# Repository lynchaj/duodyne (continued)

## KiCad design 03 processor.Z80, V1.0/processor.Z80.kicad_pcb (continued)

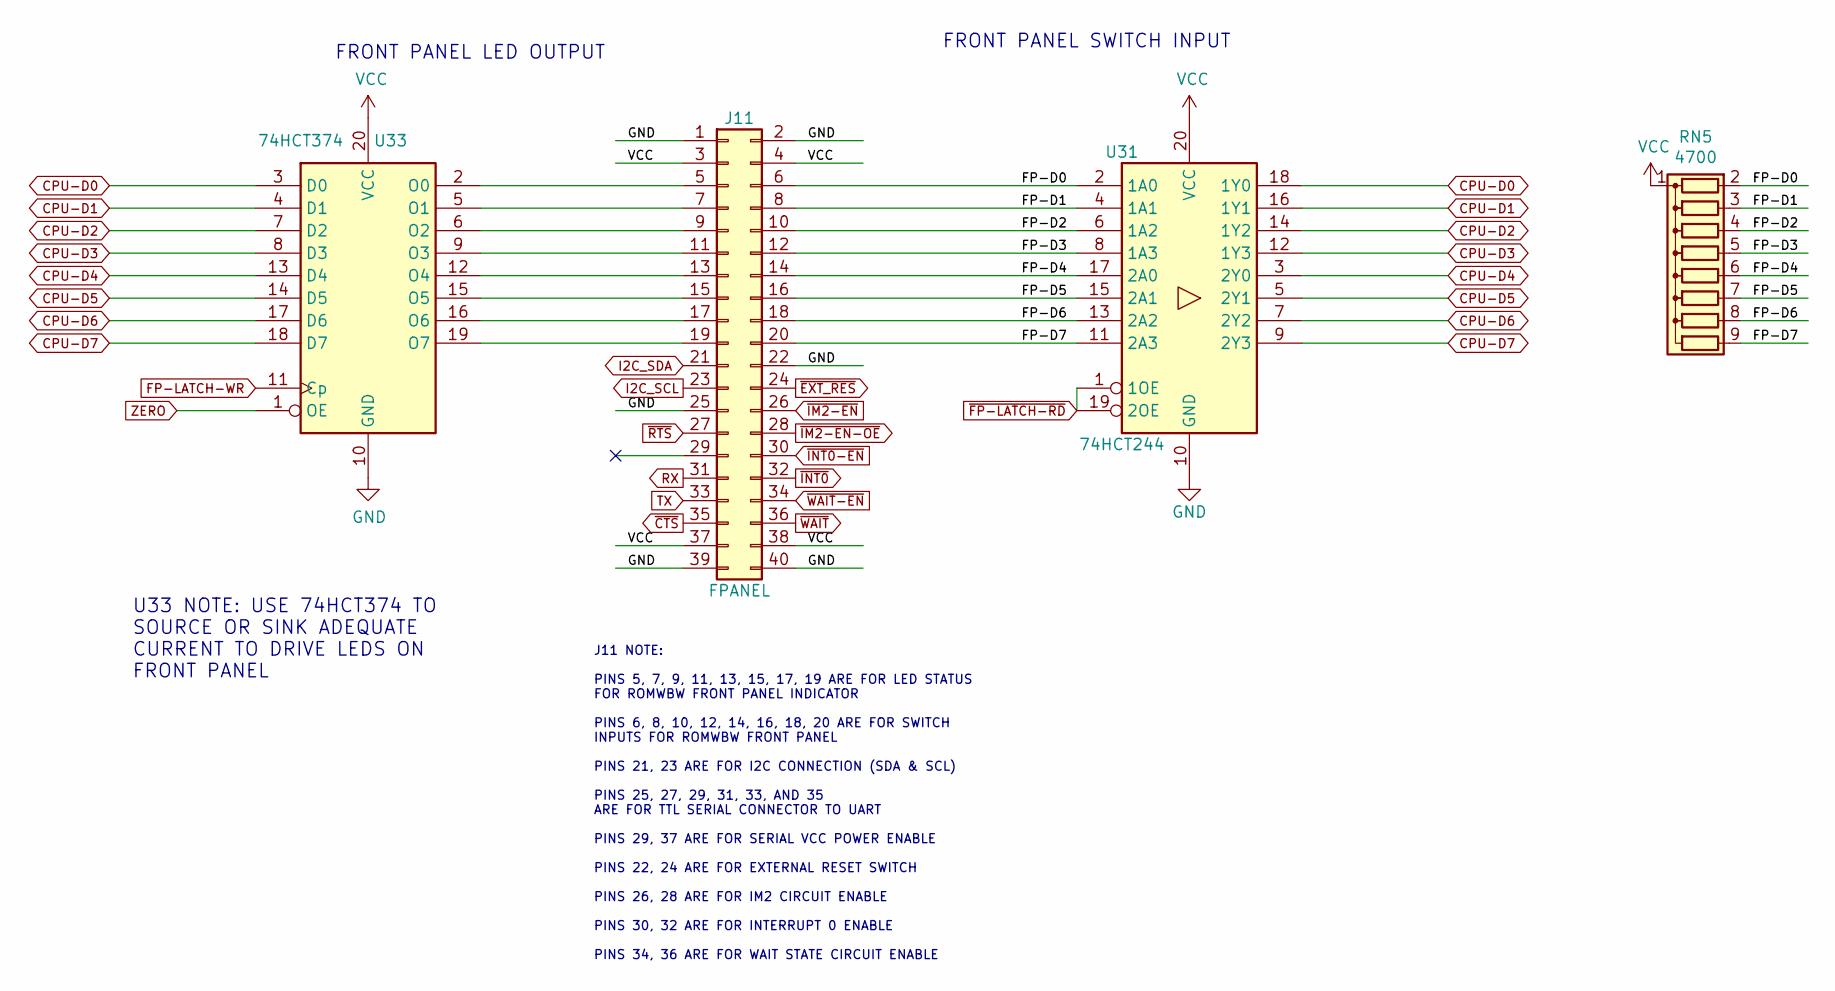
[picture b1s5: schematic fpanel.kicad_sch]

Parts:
J11: FPANEL; IDC-Header_2x20_P2.54mm_Horizontal
RN5: 4700; R_Array_SIP9
U31: 74HCT244; DIP-20_W7.62mm
U33: 74HCT374; DIP-20_W7.62mm

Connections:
/fpanel/FP-D0: J11.6, RN5.2 (R1), U31.2 (1A0)
/fpanel/FP-D1: J11.8, RN5.3 (R2), U31.4 (1A1)
/fpanel/FP-D2: J11.10, RN5.4 (R3), U31.6 (1A2)
/fpanel/FP-D3: J11.12, RN5.5 (R4), U31.8 (1A3)
/fpanel/FP-D4: J11.14, RN5.6 (R5), U31.17 (2A0)
/fpanel/FP-D5: J11.16, RN5.7 (R6), U31.15 (2A1)
/fpanel/FP-D6: J11.18, RN5.8 (R7), U31.13 (2A2)
/fpanel/FP-D7: J11.20, RN5.9 (R8), U31.11 (2A3)
CPU-D0: U31.18 (1Y0), U33.3 (D0); also elsewhere on the board
CPU-D1: U31.16 (1Y1), U33.4 (D1); also elsewhere on the board
CPU-D2: U31.14 (1Y2), U33.7 (D2); also elsewhere on the board
CPU-D3: U31.12 (1Y3), U33.8 (D3); also elsewhere on the board
CPU-D4: U31.3 (2Y0), U33.13 (D4); also elsewhere on the board
CPU-D5: U31.5 (2Y1), U33.14 (D5); also elsewhere on the board
CPU-D6: U31.7 (2Y2), U33.17 (D6); also elsewhere on the board
CPU-D7: U31.9 (2Y3), U33.18 (D7); also elsewhere on the board
FP-LATCH-WR: U33.11 (Cp); also elsewhere on the board
GND: J11.1, J11.2, J11.22, J11.25, J11.39, J11.40, U31.10 (GND), U33.10 (GND); also elsewhere on the board
I2C_SCL: J11.23; also elsewhere on the board
I2C_SDA: J11.21; also elsewhere on the board
unnamed: J11.5, U33.2 (O0)
unnamed: J11.7, U33.5 (O1)
unnamed: J11.9, U33.6 (O2)
unnamed: J11.11, U33.9 (O3)
unnamed: J11.13, U33.12 (O4)
unnamed: J11.15, U33.15 (O5)
unnamed: J11.17, U33.16 (O6)
unnamed: J11.19, U33.19 (O7)
RX: J11.31; also elsewhere on the board
TX: J11.33; also elsewhere on the board
VCC: J11.3, J11.4, J11.37, J11.38, RN5.1 (common), U31.20 (VCC), U33.20 (VCC); also elsewhere on the board
ZERO: U33.1 (OE); also elsewhere on the board
~CTS: J11.35; also elsewhere on the board
~FP-LATCH-RD: U31.1 (1OE), U31.19 (2OE); also elsewhere on the board
~IM2-EN-OE: J11.28; also elsewhere on the board
~IM2-EN: J11.26; also elsewhere on the board
~INT0: J11.32; also elsewhere on the board
~RTS: J11.27; also elsewhere on the board
~WAIT-EN: J11.34; also elsewhere on the board
~WAIT: J11.36; also elsewhere on the board

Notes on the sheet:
J11 NOTE: PINS 5, 7, 9, 11, 13, 15, 17, 19 ARE FOR LED STATUS FOR ROMWBW FRONT PANEL INDICATOR PINS 6, 8, 10, 12, 14, 16, 18, 20 ARE FOR SWITCH INPUTS FOR ROMWBW FRONT PANEL PINS 21, 23 ARE FOR I2C CONNECTION (SDA & SCL) PINS 25, 27, 29, 31, 33, AND 35 ARE FOR TTL SERIAL CONNECTOR TO UART PINS 29, 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
U33 NOTE: USE 74HCT374 TO SOURCE OR SINK ADEQUATE CURRENT TO DRIVE LEDS ON FRONT PANEL
FRONT PANEL SWITCH INPUT
FRONT PANEL LED OUTPUT

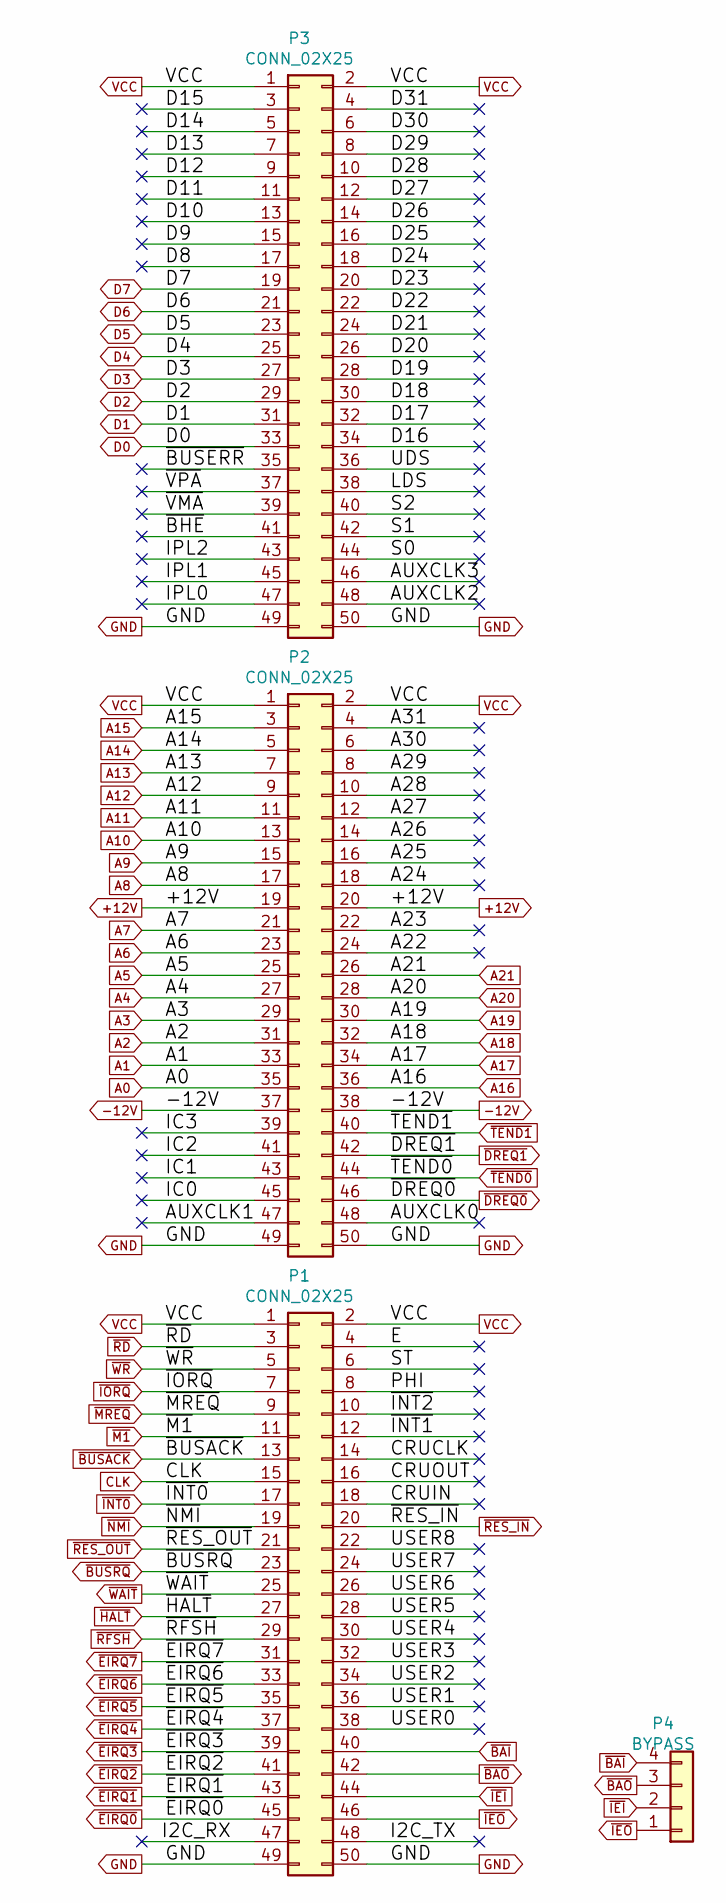
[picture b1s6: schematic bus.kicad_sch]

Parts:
P1, P2, P3: CONN_02X25; IDC-Header_2x25_P2.54mm_Horizontal
P4: BYPASS; PinHeader_1x04_P2.54mm_Vertical

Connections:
+12V: P2.19, P2.20
-12V: P2.37, P2.38
/bus/A22: P2.24
/bus/A23: P2.22
/bus/A24: P2.18
/bus/A25: P2.16
/bus/A26: P2.14
/bus/A27: P2.12
/bus/A28: P2.10
/bus/A29: P2.8
/bus/A30: P2.6
/bus/A31: P2.4
/bus/AUXCLK0: P2.48
/bus/AUXCLK1: P2.47
/bus/AUXCLK2: P3.48
/bus/AUXCLK3: P3.46
/bus/CRUCLK: P1.14
/bus/CRUIN: P1.18
/bus/CRUOUT: P1.16
/bus/D8: P3.17
/bus/D9: P3.15
/bus/D10: P3.13
/bus/D11: P3.11
/bus/D12: P3.9
/bus/D13: P3.7
/bus/D14: P3.5
/bus/D15: P3.3
/bus/D16: P3.34
/bus/D17: P3.32
/bus/D18: P3.30
/bus/D19: P3.28
/bus/D20: P3.26
/bus/D21: P3.24
/bus/D22: P3.22
/bus/D23: P3.20
/bus/D24: P3.18
/bus/D25: P3.16
/bus/D26: P3.14
/bus/D27: P3.12
/bus/D28: P3.10
/bus/D29: P3.8
/bus/D30: P3.6
/bus/D31: P3.4
/bus/E: P1.4
/bus/IC0: P2.45
/bus/IC1: P2.43
/bus/IC2: P2.41
/bus/IC3: P2.39
/bus/IPL0: P3.47
/bus/IPL1: P3.45
/bus/IPL2: P3.43
/bus/LDS: P3.38
/bus/PHI: P1.8
/bus/S0: P3.44
/bus/S1: P3.42
/bus/S2: P3.40
/bus/ST: P1.6
/bus/UDS: P3.36
/bus/USER0: P1.38
/bus/USER1: P1.36
/bus/USER2: P1.34
/bus/USER3: P1.32
/bus/USER4: P1.30
/bus/USER5: P1.28
/bus/USER6: P1.26
/bus/USER7: P1.24
/bus/USER8: P1.22
/bus/~BHE: P3.41
/bus/~BUSERR: P3.35
/bus/~INT1: P1.12
/bus/~INT2: P1.10
/bus/~VMA: P3.39
/bus/~VPA: P3.37
A0: P2.35; also elsewhere on the board
A1: P2.33; also elsewhere on the board
A2: P2.31; also elsewhere on the board
A3: P2.29; also elsewhere on the board
A4: P2.27; also elsewhere on the board
A5: P2.25; also elsewhere on the board
A6: P2.23; also elsewhere on the board
A7: P2.21; also elsewhere on the board
A8: P2.17; also elsewhere on the board
A9: P2.15; also elsewhere on the board
A10: P2.13; also elsewhere on the board
A11: P2.11; also elsewhere on the board
A12: P2.9; also elsewhere on the board
A13: P2.7; also elsewhere on the board
A14: P2.5; also elsewhere on the board
A15: P2.3; also elsewhere on the board
A16: P2.36; also elsewhere on the board
A17: P2.34; also elsewhere on the board
A18: P2.32; also elsewhere on the board
A19: P2.30; also elsewhere on the board
A20: P2.28; also elsewhere on the board
A21: P2.26; also elsewhere on the board
CLK: P1.15; also elsewhere on the board
D0: P3.33; also elsewhere on the board
D1: P3.31; also elsewhere on the board
D2: P3.29; also elsewhere on the board
D3: P3.27; also elsewhere on the board
D4: P3.25; also elsewhere on the board
D5: P3.23; also elsewhere on the board
D6: P3.21; also elsewhere on the board
D7: P3.19; also elsewhere on the board
GND: P1.49, P1.50, P2.49, P2.50, P3.49, P3.50; also elsewhere on the board
I2C_SCL: P1.47; also elsewhere on the board
I2C_SDA: P1.48; also elsewhere on the board
VCC: P1.1, P1.2, P2.1, P2.2, P3.1, P3.2; also elsewhere on the board
~BAI: P1.40, P4.4
~BAO: P1.42, P4.3; also elsewhere on the board
~BUSACK: P1.13; also elsewhere on the board
~BUSRQ: P1.23; also elsewhere on the board
~DREQ0: P2.46; also elsewhere on the board
~DREQ1: P2.42; also elsewhere on the board
~EIRQ0: P1.45; also elsewhere on the board
~EIRQ1: P1.43; also elsewhere on the board
~EIRQ2: P1.41; also elsewhere on the board
~EIRQ3: P1.39; also elsewhere on the board
~EIRQ4: P1.37; also elsewhere on the board
~EIRQ5: P1.35; also elsewhere on the board
~EIRQ6: P1.33; also elsewhere on the board
~EIRQ7: P1.31; also elsewhere on the board
~HALT: P1.27; also elsewhere on the board
~IEI: P1.44, P4.2; also elsewhere on the board
~IEO: P1.46, P4.1; also elsewhere on the board
~INT0: P1.17; also elsewhere on the board
~IORQ: P1.7; also elsewhere on the board
~M1: P1.11; also elsewhere on the board
~MREQ: P1.9; also elsewhere on the board
~NMI: P1.19; also elsewhere on the board
~RD: P1.3; also elsewhere on the board
~RES_IN: P1.20; also elsewhere on the board
~RES_OUT: P1.21; also elsewhere on the board
~RFSH: P1.29; also elsewhere on the board
~TEND0: P2.44; also elsewhere on the board
~TEND1: P2.40; also elsewhere on the board
~WAIT: P1.25; also elsewhere on the board
~WR: P1.5; also elsewhere on the board

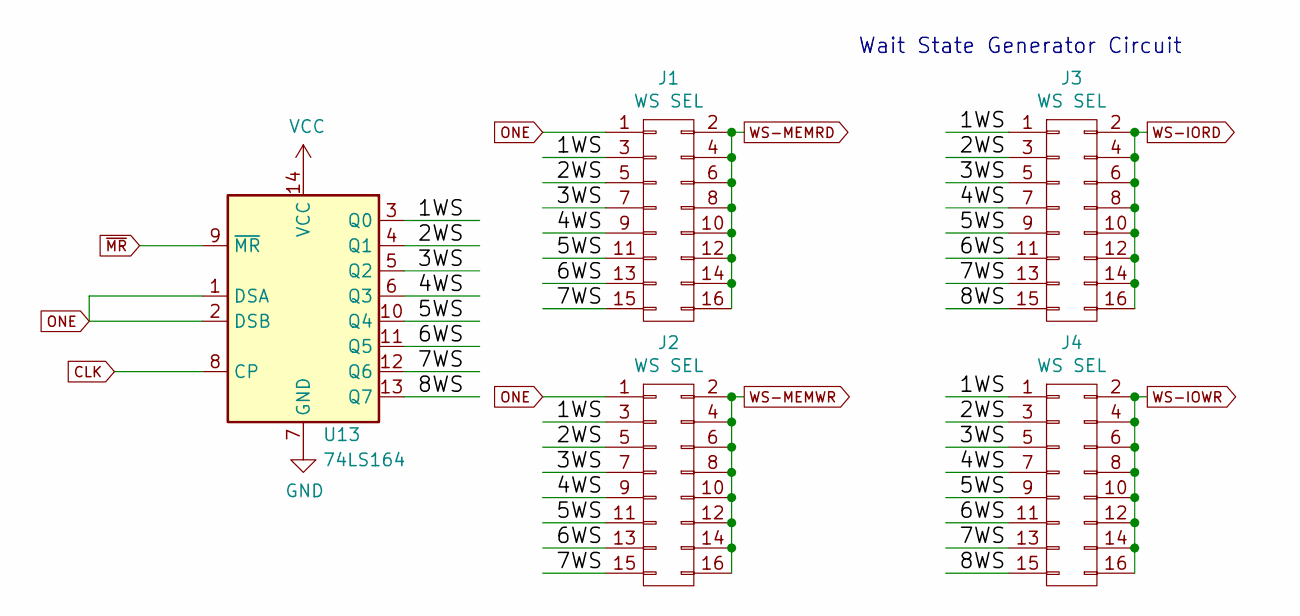
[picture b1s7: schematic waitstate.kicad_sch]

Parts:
J1, J2, J3, J4: WS SEL; PinHeader_2x08_P2.54mm_Vertical
U13: 74LS164; DIP-14_W7.62mm

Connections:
/waitstate/1WS: J1.3, J2.3, J3.1, J4.1, U13.3 (Q0)
/waitstate/2WS: J1.5, J2.5, J3.3, J4.3, U13.4 (Q1)
/waitstate/3WS: J1.7, J2.7, J3.5, J4.5, U13.5 (Q2)
/waitstate/4WS: J1.9, J2.9, J3.7, J4.7, U13.6 (Q3)
/waitstate/5WS: J1.11, J2.11, J3.9, J4.9, U13.10 (Q4)
/waitstate/6WS: J1.13, J2.13, J3.11, J4.11, U13.11 (Q5)
/waitstate/7WS: J1.15, J2.15, J3.13, J4.13, U13.12 (Q6)
/waitstate/8WS: J3.15, J4.15, U13.13 (Q7)
CLK: U13.8 (CP); also elsewhere on the board
GND: U13.7 (GND); also elsewhere on the board
ONE: J1.1, J2.1, U13.1 (DSA), U13.2 (DSB); also elsewhere on the board
VCC: U13.14 (VCC); also elsewhere on the board
WS-IORD: J3.2, J3.4, J3.6, J3.8, J3.10, J3.12, J3.14, J3.16; also elsewhere on the board
WS-IOWR: J4.2, J4.4, J4.6, J4.8, J4.10, J4.12, J4.14, J4.16; also elsewhere on the board
WS-MEMRD: J1.2, J1.4, J1.6, J1.8, J1.10, J1.12, J1.14, J1.16; also elsewhere on the board
WS-MEMWR: J2.2, J2.4, J2.6, J2.8, J2.10, J2.12, J2.14, J2.16; also elsewhere on the board
~MR: U13.9 (~MR); also elsewhere on the board

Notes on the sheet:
Wait State Generator Circuit

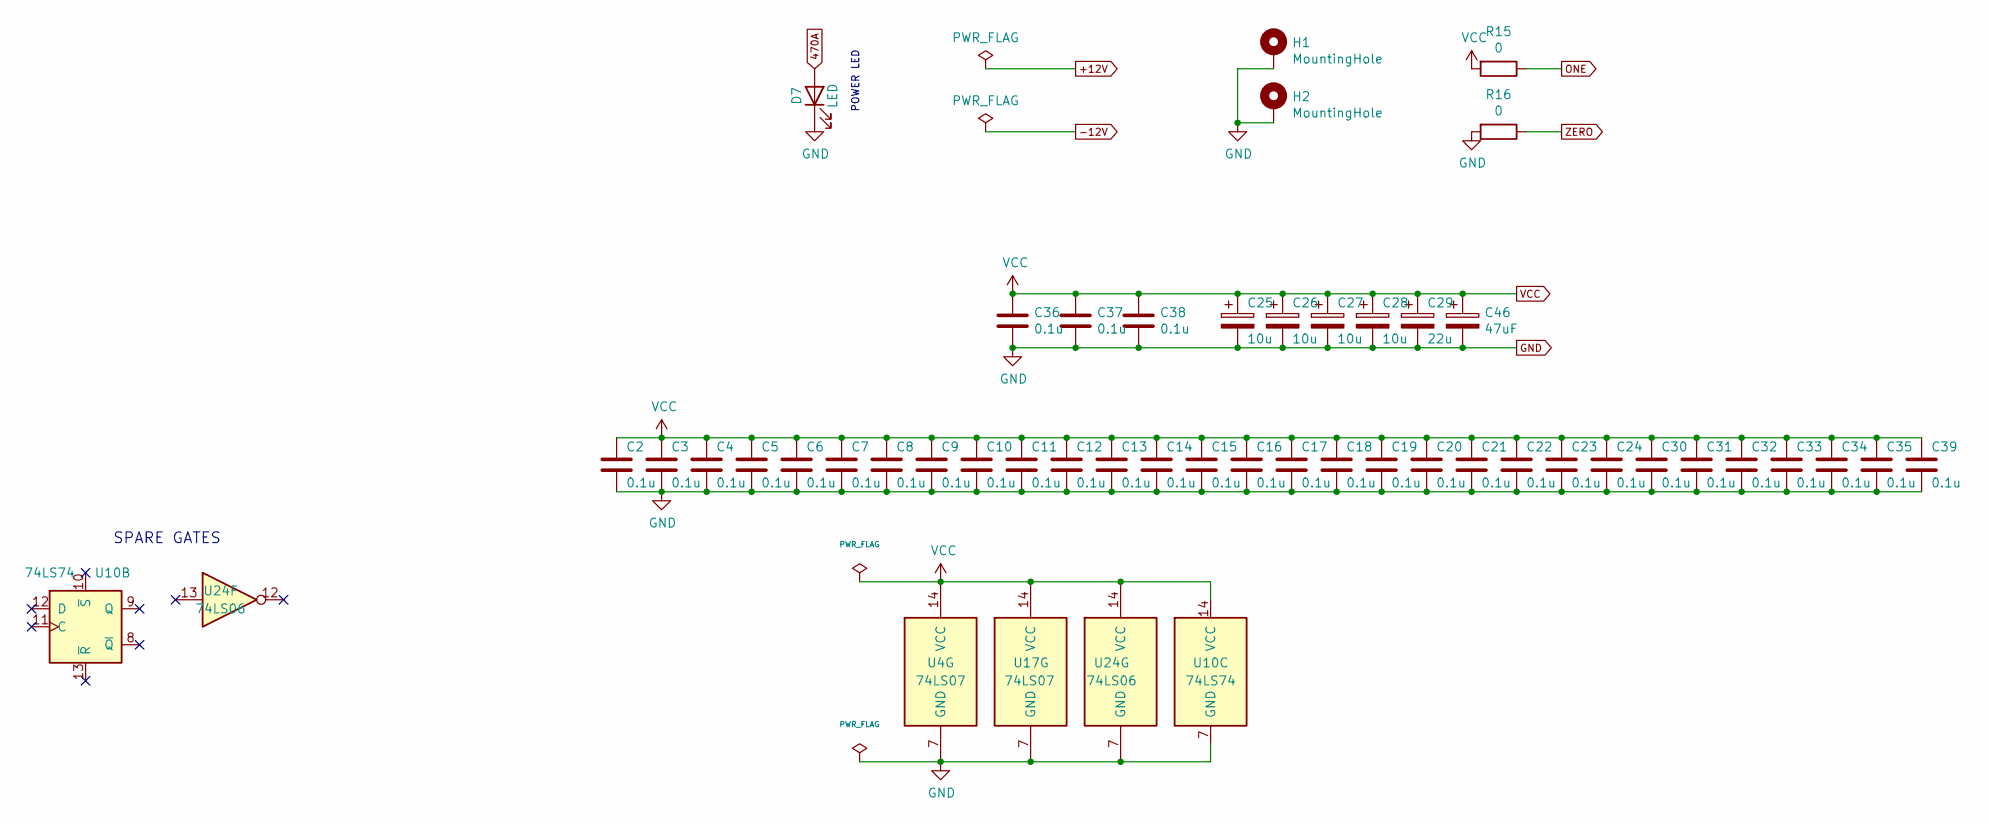
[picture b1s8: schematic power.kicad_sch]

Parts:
C2, C3, C4, C5, C6, C7, C8, C9, C10, C11, C12, C13, C14, C15, C16, C17, C18, C19, C20, C21, C22, C23, C24, C30, C31, C32, C33, C34, C35, C36, C37, C38, C39: 0.1u; C_Disc_D5.0mm_W2.5mm_P5.00mm
C25, C26, C27, C28: 10u; CP_Radial_D5.0mm_P2.50mm
C29: 22u; CP_Radial_D6.3mm_P2.50mm
C46: 47uF; CP_Radial_D5.0mm_P2.50mm
D7: LED; LED_D3.0mm_Horizontal_O3.81mm_Z2.0mm
H1, H2: MountingHole; MountingHole_3.2mm_M3_Pad
R15, R16: 0; R_Axial_DIN0207_L6.3mm_D2.5mm_P7.62mm_Horizontal
U4, U17: 74LS07; DIP-14_W7.62mm
U10: 74LS74; DIP-14_W7.62mm
U24: 74LS06; DIP-14_W7.62mm

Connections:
470A: D7.2 (A); also elsewhere on the board
GND: C2.2, C3.2, C4.2, C5.2, C6.2, C7.2, C8.2, C9.2, C10.2, C11.2, C12.2, C13.2, C14.2, C15.2, C16.2, C17.2, C18.2, C19.2, C20.2, C21.2, C22.2, C23.2, C24.2, C25.2, C26.2, C27.2, C28.2, C29.2, C30.2, C31.2, C32.2, C33.2, C34.2, C35.2, C36.2, C37.2, C38.2, C39.2, C46.2, D7.1 (K), H1.1, H2.1, R16.2, U4.7 (GND), U10.7 (GND), U17.7 (GND), U24.7 (GND); also elsewhere on the board
INT-I2C: U24.13; also elsewhere on the board
unnamed 185: U24.12; also elsewhere on the board
VCC: C2.1, C3.1, C4.1, C5.1, C6.1, C7.1, C8.1, C9.1, C10.1, C11.1, C12.1, C13.1, C14.1, C15.1, C16.1, C17.1, C18.1, C19.1, C20.1, C21.1, C22.1, C23.1, C24.1, C25.1, C26.1, C27.1, C28.1, C29.1, C30.1, C31.1, C32.1, C33.1, C34.1, C35.1, C36.1, C37.1, C38.1, C39.1, C46.1, R15.2, U4.14 (VCC), U10.14 (VCC), U17.14 (VCC), U24.14 (VCC); also elsewhere on the board

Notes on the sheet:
POWER LED
SPARE GATES

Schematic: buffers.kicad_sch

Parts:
JP7: BUS CPU; PinHeader_2x04_P2.54mm_Vertical
R8, R9: 4700; R_Axial_DIN0207_L6.3mm_D2.5mm_P7.62mm_Horizontal
R10: 1800; R_Axial_DIN0207_L6.3mm_D2.5mm_P7.62mm_Horizontal
RN1, RN4: 4700; R_Array_SIP9
U1, U5, U6, U11, U23: 74LS244; DIP-20_W7.62mm
U8: 74LS245; DIP-20_W7.62mm

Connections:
A0: U1.18 (1Y0); also elsewhere on the board
A1: U1.16 (1Y1); also elsewhere on the board
A2: U1.14 (1Y2); also elsewhere on the board
A3: U1.12 (1Y3); also elsewhere on the board
A4: U1.3 (2Y0); also elsewhere on the board
A5: U1.5 (2Y1); also elsewhere on the board
A6: U1.7 (2Y2); also elsewhere on the board
A7: U1.9 (2Y3); also elsewhere on the board
A8: U5.18 (1Y0); also elsewhere on the board
A9: U5.16 (1Y1); also elsewhere on the board
A10: U5.14 (1Y2); also elsewhere on the board
A11: U5.12 (1Y3); also elsewhere on the board
A12: U5.3 (2Y0); also elsewhere on the board
A13: U5.5 (2Y1); also elsewhere on the board
A14: U5.7 (2Y2); also elsewhere on the board
A15: U5.9 (2Y3); also elsewhere on the board
A16: U23.18 (1Y0); also elsewhere on the board
A17: U23.16 (1Y1); also elsewhere on the board
A18: U23.14 (1Y2); also elsewhere on the board
A19: U23.12 (1Y3); also elsewhere on the board
A20: U23.3 (2Y0); also elsewhere on the board
A21: U23.5 (2Y1); also elsewhere on the board
BUSACK: U1.1 (1OE), U1.19 (2OE), U5.1 (1OE), U5.19 (2OE), U11.19 (2OE), U23.1 (1OE), U23.19 (2OE); also elsewhere on the board
CLK: U6.16 (1Y1); also elsewhere on the board
CPU-A0: U1.2 (1A0); also elsewhere on the board
CPU-A1: U1.4 (1A1); also elsewhere on the board
CPU-A2: U1.6 (1A2); also elsewhere on the board
CPU-A3: U1.8 (1A3); also elsewhere on the board
CPU-A4: U1.17 (2A0); also elsewhere on the board
CPU-A5: U1.15 (2A1); also elsewhere on the board
CPU-A6: U1.13 (2A2); also elsewhere on the board
CPU-A7: U1.11 (2A3); also elsewhere on the board
CPU-A8: U5.2 (1A0); also elsewhere on the board
CPU-A9: U5.4 (1A1); also elsewhere on the board
CPU-A10: U5.6 (1A2); also elsewhere on the board
CPU-A11: U5.8 (1A3); also elsewhere on the board
CPU-A12: U5.17 (2A0); also elsewhere on the board
CPU-A13: U5.15 (2A1); also elsewhere on the board
CPU-D0: U8.2 (A0); also elsewhere on the board
CPU-D1: U8.3 (A1); also elsewhere on the board
CPU-D2: U8.4 (A2); also elsewhere on the board
CPU-D3: U8.5 (A3); also elsewhere on the board
CPU-D4: U8.6 (A4); also elsewhere on the board
CPU-D5: U8.7 (A5); also elsewhere on the board
CPU-D6: U8.8 (A6); also elsewhere on the board
CPU-D7: U8.9 (A7); also elsewhere on the board
D0: U8.18 (B0); also elsewhere on the board
D1: U8.17 (B1); also elsewhere on the board
D2: U8.16 (B2); also elsewhere on the board
D3: U8.15 (B3); also elsewhere on the board
D4: U8.14 (B4); also elsewhere on the board
D5: U8.13 (B5); also elsewhere on the board
D6: U8.12 (B6); also elsewhere on the board
D7: U8.11 (B7); also elsewhere on the board
DATA-DIR: U8.1 (A->B); also elsewhere on the board
GND: U1.10 (GND), U5.10 (GND), U6.10 (GND), U8.10 (GND), U11.10 (GND), U23.10 (GND); also elsewhere on the board
unnamed: JP7.1, RN4.6 (R5)
unnamed: JP7.3, RN4.7 (R6)
unnamed: JP7.5, RN4.8 (R7)
unnamed: JP7.7, RN4.9 (R8)
RAW-CLK: U6.4 (1A1); also elsewhere on the board
SEL-A14: U5.13 (2A2); also elsewhere on the board
SEL-A15: U5.11 (2A3); also elsewhere on the board
VCC: R8.1, R9.1, R10.1, RN1.1 (common), RN4.1 (common), U1.20 (VCC), U5.20 (VCC), U6.20 (VCC), U8.20 (VCC), U11.20 (VCC), U23.20 (VCC); also elsewhere on the board
ZERO: U6.1 (1OE), U6.19 (2OE), U11.1 (1OE); also elsewhere on the board
mA16: U23.2 (1A0); also elsewhere on the board
mA17: U23.4 (1A1); also elsewhere on the board
mA18: U23.6 (1A2); also elsewhere on the board
mA19: U23.8 (1A3); also elsewhere on the board
mA20: U23.17 (2A0); also elsewhere on the board
mA21: U23.15 (2A1); also elsewhere on the board
~BAO: RN1.9 (R8), RN4.2 (R1); also elsewhere on the board
~BUS-EN: U8.19 (CE); also elsewhere on the board
~BUSACK: U11.18 (1Y0); also elsewhere on the board
~BUSRQ: R10.2, U6.15 (2A1); also elsewhere on the board
~CPU-BUSRQ: U6.5 (2Y1); also elsewhere on the board
~CPU-HALT: U11.4 (1A1); also elsewhere on the board
~CPU-INT: U6.12 (1Y3); also elsewhere on the board
~CPU-IORQ: RN1.8 (R7), U11.17 (2A0); also elsewhere on the board
~CPU-M1: U11.8 (1A3); also elsewhere on the board
~CPU-MREQ: U11.15 (2A1); also elsewhere on the board
~CPU-NMI: U6.14 (1Y2); also elsewhere on the board
~CPU-RD: U11.11 (2A3); also elsewhere on the board
~CPU-RESET: RN4.5 (R4), U6.18 (1Y0); also elsewhere on the board
~CPU-RFSH: U11.6 (1A2); also elsewhere on the board
~CPU-WAIT: U6.3 (2Y0); also elsewhere on the board
~CPU-WR: U11.13 (2A2); also elsewhere on the board
~DMA-ADDR: RN1.7 (R6); also elsewhere on the board
~DMA-BAO2: U11.2 (1A0); also elsewhere on the board
~DMA-IEI1: U6.9 (2Y3); also elsewhere on the board
~DREQ0: R8.2; also elsewhere on the board
~DREQ1: R9.2; also elsewhere on the board
~HALT: U11.16 (1Y1); also elsewhere on the board
~IEI: RN1.3 (R2), U6.11 (2A3); also elsewhere on the board
~INT0: RN1.5 (R4), U6.8 (1A3); also elsewhere on the board
~IORQ: JP7.2, U11.3 (2Y0); also elsewhere on the board
~M1: U11.12 (1Y3); also elsewhere on the board
~MREQ: JP7.4, U11.5 (2Y1); also elsewhere on the board
~NMI: RN1.4 (R3), U6.6 (1A2); also elsewhere on the board
~RD: JP7.8, U11.9 (2Y3); also elsewhere on the board
~RES_OUT: RN1.2 (R1), U6.2 (1A0); also elsewhere on the board
~RFSH: U11.14 (1Y2); also elsewhere on the board
~TEND0: RN4.3 (R2); also elsewhere on the board
~TEND1: RN4.4 (R3); also elsewhere on the board
~WAIT: RN1.6 (R5), U6.17 (2A0); also elsewhere on the board
~WR: JP7.6, U11.7 (2Y2); also elsewhere on the board

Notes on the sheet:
Z80 BUS INTERFACE

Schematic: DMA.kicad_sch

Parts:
D6, D8, D9, D10, D11, D12: LED; LED_D3.0mm_Horizontal_O3.81mm_Z2.0mm
JP4: IO PORT ADDR; PinHeader_2x06_P2.54mm_Vertical
JP5: INT EN; PinHeader_1x02_P2.54mm_Horizontal
JP6: DMA2 BYPASS; PinHeader_1x04_P2.54mm_Vertical
JP8: DMA1 BYPASS; PinHeader_1x04_P2.54mm_Vertical
JP9: BAO SEL; PinHeader_1x03_P2.54mm_Vertical
NT1, NT2: NetTie_2; NetTie-2_THT_Pad0.3mm
R21: 470; R_Axial_DIN0207_L6.3mm_D2.5mm_P7.62mm_Horizontal
RN3: 10K; R_Array_SIP9
RN6: 4700; R_Array_SIP9
RN9: 470; R_Array_SIP9
U4, U17: 74LS07; DIP-14_W7.62mm
U18, U19: DMA-PLCC-44-CMOS; PLCC-44_THT-Socket; Manufacturer_Part_Number Z84C4206PEG; Mouser Part Number 692-Z84C4206PEG
U20: 74LS175; DIP-16_W7.62mm
U21: 74LS688; DIP-20_W7.62mm
U24: 74LS06
U32: ATtiny13-20PU; DIP-8_W7.62mm

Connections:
10KA: RN3.9 (R8); also elsewhere on the board
470A: RN9.2 (R1); also elsewhere on the board
470B: D6.2 (A), RN9.3 (R2)
470C: RN9.4 (R3); also elsewhere on the board
470D: RN9.5 (R4); also elsewhere on the board
470E: D11.2 (A), RN9.6 (R5)
470F: D8.2 (A), RN9.7 (R6)
470G: D9.2 (A), RN9.8 (R7)
470H: D12.2 (A), RN9.9 (R8)
/DMA/GND-DMA1: NT1.2, U19.34 (GND)
/DMA/GND-DMA2: NT2.2, U18.34 (GND)
CLK: U18.8 (CLK), U19.8 (CLK); also elsewhere on the board
CPU-A0: U18.7 (A0), U19.7 (A0); also elsewhere on the board
CPU-A1: U18.5 (A1), U19.5 (A1); also elsewhere on the board
CPU-A2: U18.4 (A2), U19.4 (A2), U21.6 (P2); also elsewhere on the board
CPU-A3: U18.3 (A3), U19.3 (A3), U21.8 (P3); also elsewhere on the board
CPU-A4: U18.2 (A4), U19.2 (A4), U21.11 (P4); also elsewhere on the board
CPU-A5: U18.1 (A5), U19.1 (A5), U21.13 (P5); also elsewhere on the board
CPU-A6: U18.44 (A6), U19.44 (A6), U21.15 (P6); also elsewhere on the board
CPU-A7: U18.43 (A7), U19.43 (A7), U21.17 (P7); also elsewhere on the board
CPU-A8: U18.26 (A8), U19.26 (A8); also elsewhere on the board
CPU-A9: U18.25 (A9), U19.25 (A9); also elsewhere on the board
CPU-A10: U18.24 (A10), U19.24 (A10); also elsewhere on the board
CPU-A11: U18.23 (A11), U19.23 (A11); also elsewhere on the board
CPU-A12: U18.22 (A12), U19.22 (A12); also elsewhere on the board
CPU-A13: U18.21 (A13), U19.21 (A13); also elsewhere on the board
CPU-A14: U18.20 (A14), U19.20 (A14); also elsewhere on the board
CPU-A15: U18.19 (A15), U19.19 (A15); also elsewhere on the board
CPU-D0: U18.39 (D0), U19.39 (D0), U20.4 (D0); also elsewhere on the board
CPU-D1: U18.38 (D1), U19.38 (D1), U20.5 (D1); also elsewhere on the board
CPU-D2: U18.37 (D2), U19.37 (D2), U20.12 (D2); also elsewhere on the board
CPU-D3: U18.36 (D3), U19.36 (D3), U20.13 (D3); also elsewhere on the board
CPU-D4: U18.35 (D4), U19.35 (D4); also elsewhere on the board
CPU-D5: U18.32 (D5), U19.32 (D5); also elsewhere on the board
CPU-D6: U18.33 (D6), U19.33 (D6); also elsewhere on the board
CPU-D7: U18.31 (D7), U19.31 (D7); also elsewhere on the board
DATA_XFER: U32.6 (PB1); also elsewhere on the board
DMA-RDY1: U19.27 (RDY), U24.3; also elsewhere on the board
DMA-RDY2: U18.27 (RDY), U24.1; also elsewhere on the board
GND: D10.1 (K), NT1.1, NT2.1, U20.8 (GND), U21.10 (GND), U32.4 (GND); also elsewhere on the board
unnamed: D8.1 (K), U24.4
unnamed: D9.1 (K), U17.12
unnamed: D10.2 (A), R21.1
unnamed: D11.1 (K), U17.8
unnamed: D12.1 (K), U24.2
unnamed: JP4.2, RN3.2 (R1), U21.18 (R7)
unnamed: JP4.4, RN3.3 (R2), U21.16 (R6)
unnamed: JP4.6, RN3.4 (R3), U21.14 (R5)
unnamed: JP4.8, RN3.5 (R4), U21.12 (R4)
unnamed: JP4.10, RN3.6 (R5), U21.9 (R3)
unnamed: JP4.12, RN3.7 (R6), U21.7 (R2)
unnamed: JP9.2, U17.5
unnamed: R21.2, U32.7 (PB2)
unnamed: RN3.8 (R7), U21.3 (R0), U21.4 (P1), U21.5 (R1)
RDY_Q0: U20.2 (Q0); also elsewhere on the board
RDY_Q1: U20.7 (Q1); also elsewhere on the board
VCC: RN3.1 (common), RN6.1 (common), RN9.1 (common), U18.13 (VCC), U19.13 (VCC), U20.16 (VCC), U21.20 (VCC), U32.8 (VCC); also elsewhere on the board
ZERO: JP4.1, JP4.3, JP4.5, JP4.7, JP4.9, JP4.11; also elsewhere on the board
~BAO: U17.6; also elsewhere on the board
~BUSRQ: U18.17 (~BUSREQ), U19.17 (~BUSREQ); also elsewhere on the board
~CPU-BUSACK: JP8.3, U19.16 (~BAI); also elsewhere on the board
~CPU-IORQ: U18.11 (~IORQ), U19.11 (~IORQ), U21.1 (G); also elsewhere on the board
~CPU-M1: U18.30 (~M1), U19.30 (~M1), U21.2 (P0); also elsewhere on the board
~CPU-MREQ: U18.14 (~MREQ), U19.14 (~MREQ); also elsewhere on the board
~CPU-RD: U18.10 (~RD), U19.10 (~RD); also elsewhere on the board
~CPU-RESET: U20.1 (~Mr), U32.1 (~RESET/PB5); also elsewhere on the board
~CPU-WR: U18.9 (~WR), U19.9 (~WR); also elsewhere on the board
~DMA-ADDR: U21.19 (P=R); also elsewhere on the board
~DMA-BAO1: JP6.3, JP8.4, JP9.1, RN6.6 (R5), U18.16 (~BAI), U19.15 (~BA0)
~DMA-BAO2: JP6.4, JP9.3, RN6.8 (R7), U18.15 (~BA0); also elsewhere on the board
~DMA-CS1: U17.9, U19.18 (~CE/WAIT); also elsewhere on the board
~DMA-CS2: U17.13, U18.18 (~CE/WAIT); also elsewhere on the board
~DMA-IEI1: JP8.1, U19.42 (IEI); also elsewhere on the board
~DMA-IEO1: JP6.1, JP8.2, RN6.7 (R6), U18.42 (IEI), U19.40 (IEO)
~DMA-IEO2: JP6.2, RN6.9 (R8), U18.40 (IEO); also elsewhere on the board
~DMA-INT-PULSE1: RN6.3 (R2), U4.3, U17.1, U19.41 (~INT/PULSE); also elsewhere on the board
~DMA-INT-PULSE2: RN6.4 (R3), U4.1, U17.3, U18.41 (~INT/PULSE); also elsewhere on the board
~DMA-RESET1: U19.12 (~RESET); also elsewhere on the board
~DMA-RESET2: U18.12 (~RESET); also elsewhere on the board
~DMA_RDY_WR: U20.9 (Cp); also elsewhere on the board
~IEO: RN6.2 (R1), U17.10; also elsewhere on the board
~IM2-IEO: U17.11; also elsewhere on the board
~IM2-INT: U4.9; also elsewhere on the board
~INT-I2C: RN6.5 (R4); also elsewhere on the board
~TEND0: U4.4; also elsewhere on the board
~TEND1: U4.2; also elsewhere on the board
~USR-RESET1: U20.11 (~Q2); also elsewhere on the board
~USR-RESET2: U20.14 (~Q3); also elsewhere on the board

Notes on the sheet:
INTERRUPT
DMA1 READY LED
NOTE: DMA2 BYPASS INSTALL JUMPERS ON PINS 1-2 AND 3-4 IF NO DMA
NOTE: DMA1 BYPASS INSTALL JUMPERS ON PINS 1-2 AND 3-4 IF NO DMA
IO ADDRESS SELECT CIRCUIT
DMA Transfer LED triggered whenever a DMA transfer is in progress and the pulse signal is active. DMA software configuration needs to program the activation of the pulse signal.
DMA1 CHIP SELECT LED
DMA XFER
INTERRUPT FILTER CIRCUIT
DMA2 READY LED
DMA2 CHIP SELECT LED
TEND IS AN OUTPUT FROM DMA
NOTE: PROCESSOR BOARD MUST BE THE START OF THE BAI/BAO CHAIN. BAO ORIGINATES WITH CPU BUSACK. NO BAI SIGNAL TO PROCESSOR BOARD.
Z80 DMA IO PORT DECODER
Note: IO Address Port $40-$43 1-2 =on - A7 (low) 3-4 =off - A6 (high) 5-6 =on - A5 (low) 7-8 =on - A4 (low) 9-10 =on - A3 (low) 11-12 =on - A2 (low)

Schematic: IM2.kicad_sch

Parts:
JP3: IM2 EN; PinHeader_1x02_P2.54mm_Vertical
RN2: 4700; R_Array_SIP9
U15: 74LS148; DIP-16_W7.62mm
U16: 74LS373; DIP-20_W7.62mm

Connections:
D0: U16.2 (O0); also elsewhere on the board
D1: U16.5 (O1); also elsewhere on the board
D2: U16.6 (O2); also elsewhere on the board
D3: U16.9 (O3); also elsewhere on the board
D4: U16.12 (O4); also elsewhere on the board
D5: U16.15 (O5); also elsewhere on the board
D6: U16.16 (O6); also elsewhere on the board
D7: U16.19 (O7); also elsewhere on the board
GND: U15.8 (GND), U16.10 (GND); also elsewhere on the board
unnamed: U15.6 (S2), U16.8 (D3)
unnamed: U15.7 (S1), U16.7 (D2)
unnamed: U15.9 (S0), U16.4 (D1)
VCC: RN2.1 (common), U15.16 (VCC), U16.20 (VCC); also elsewhere on the board
ZERO: U15.5 (EI), U16.3 (D0), U16.13 (D4), U16.14 (D5), U16.17 (D6), U16.18 (D7); also elsewhere on the board
~CPU-M1: U16.11 (LE); also elsewhere on the board
~EIRQ0: RN2.9 (R8), U15.10 (IO); also elsewhere on the board
~EIRQ1: RN2.8 (R7), U15.11 (I1); also elsewhere on the board
~EIRQ2: RN2.7 (R6), U15.12 (I2); also elsewhere on the board
~EIRQ3: RN2.6 (R5), U15.13 (I3); also elsewhere on the board
~EIRQ4: RN2.5 (R4), U15.1 (I4); also elsewhere on the board
~EIRQ5: RN2.4 (R3), U15.2 (I5); also elsewhere on the board
~EIRQ6: RN2.3 (R2), U15.3 (I6); also elsewhere on the board
~EIRQ7: RN2.2 (R1), U15.4 (I7); also elsewhere on the board
~IM2-EN-OE: JP3.1 (A), U16.1 (OE); also elsewhere on the board
~IM2-INT: U15.14 (GS); also elsewhere on the board

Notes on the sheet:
Interrupt Mode 2 (IM2) Circuit

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
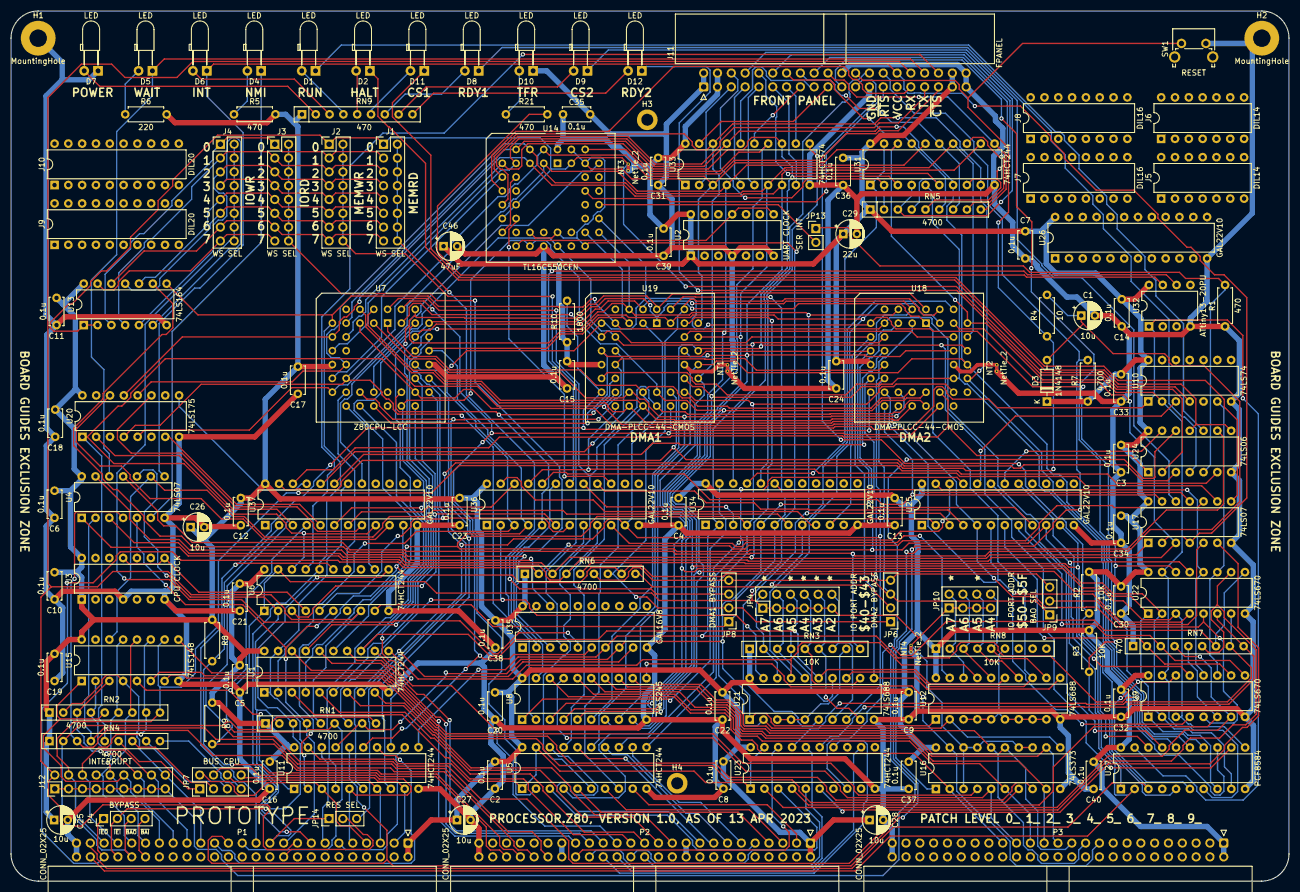
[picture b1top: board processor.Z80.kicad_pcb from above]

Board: 2 copper layers, 235.0 x 160.0 mm, 140 parts (0 on the bottom side), 245 nets.

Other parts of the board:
C40: 0.1u; C_Disc_D5.0mm_W2.5mm_P5.00mm
NT3, NT4: NetTie_2; NetTie-2_THT_Pad0.3mm
R7: 4700; R_Axial_DIN0207_L6.3mm_D2.5mm_P7.62mm_Horizontal

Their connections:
GND: C40.2, NT4.1; also elsewhere on the board
ONE: NT3.2; also elsewhere on the board
VCC: C40.1, NT3.1, R7.1; also elsewhere on the board
ZERO: NT4.2; also elsewhere on the board
~IM2-EN-OE: R7.2; also elsewhere on the board
